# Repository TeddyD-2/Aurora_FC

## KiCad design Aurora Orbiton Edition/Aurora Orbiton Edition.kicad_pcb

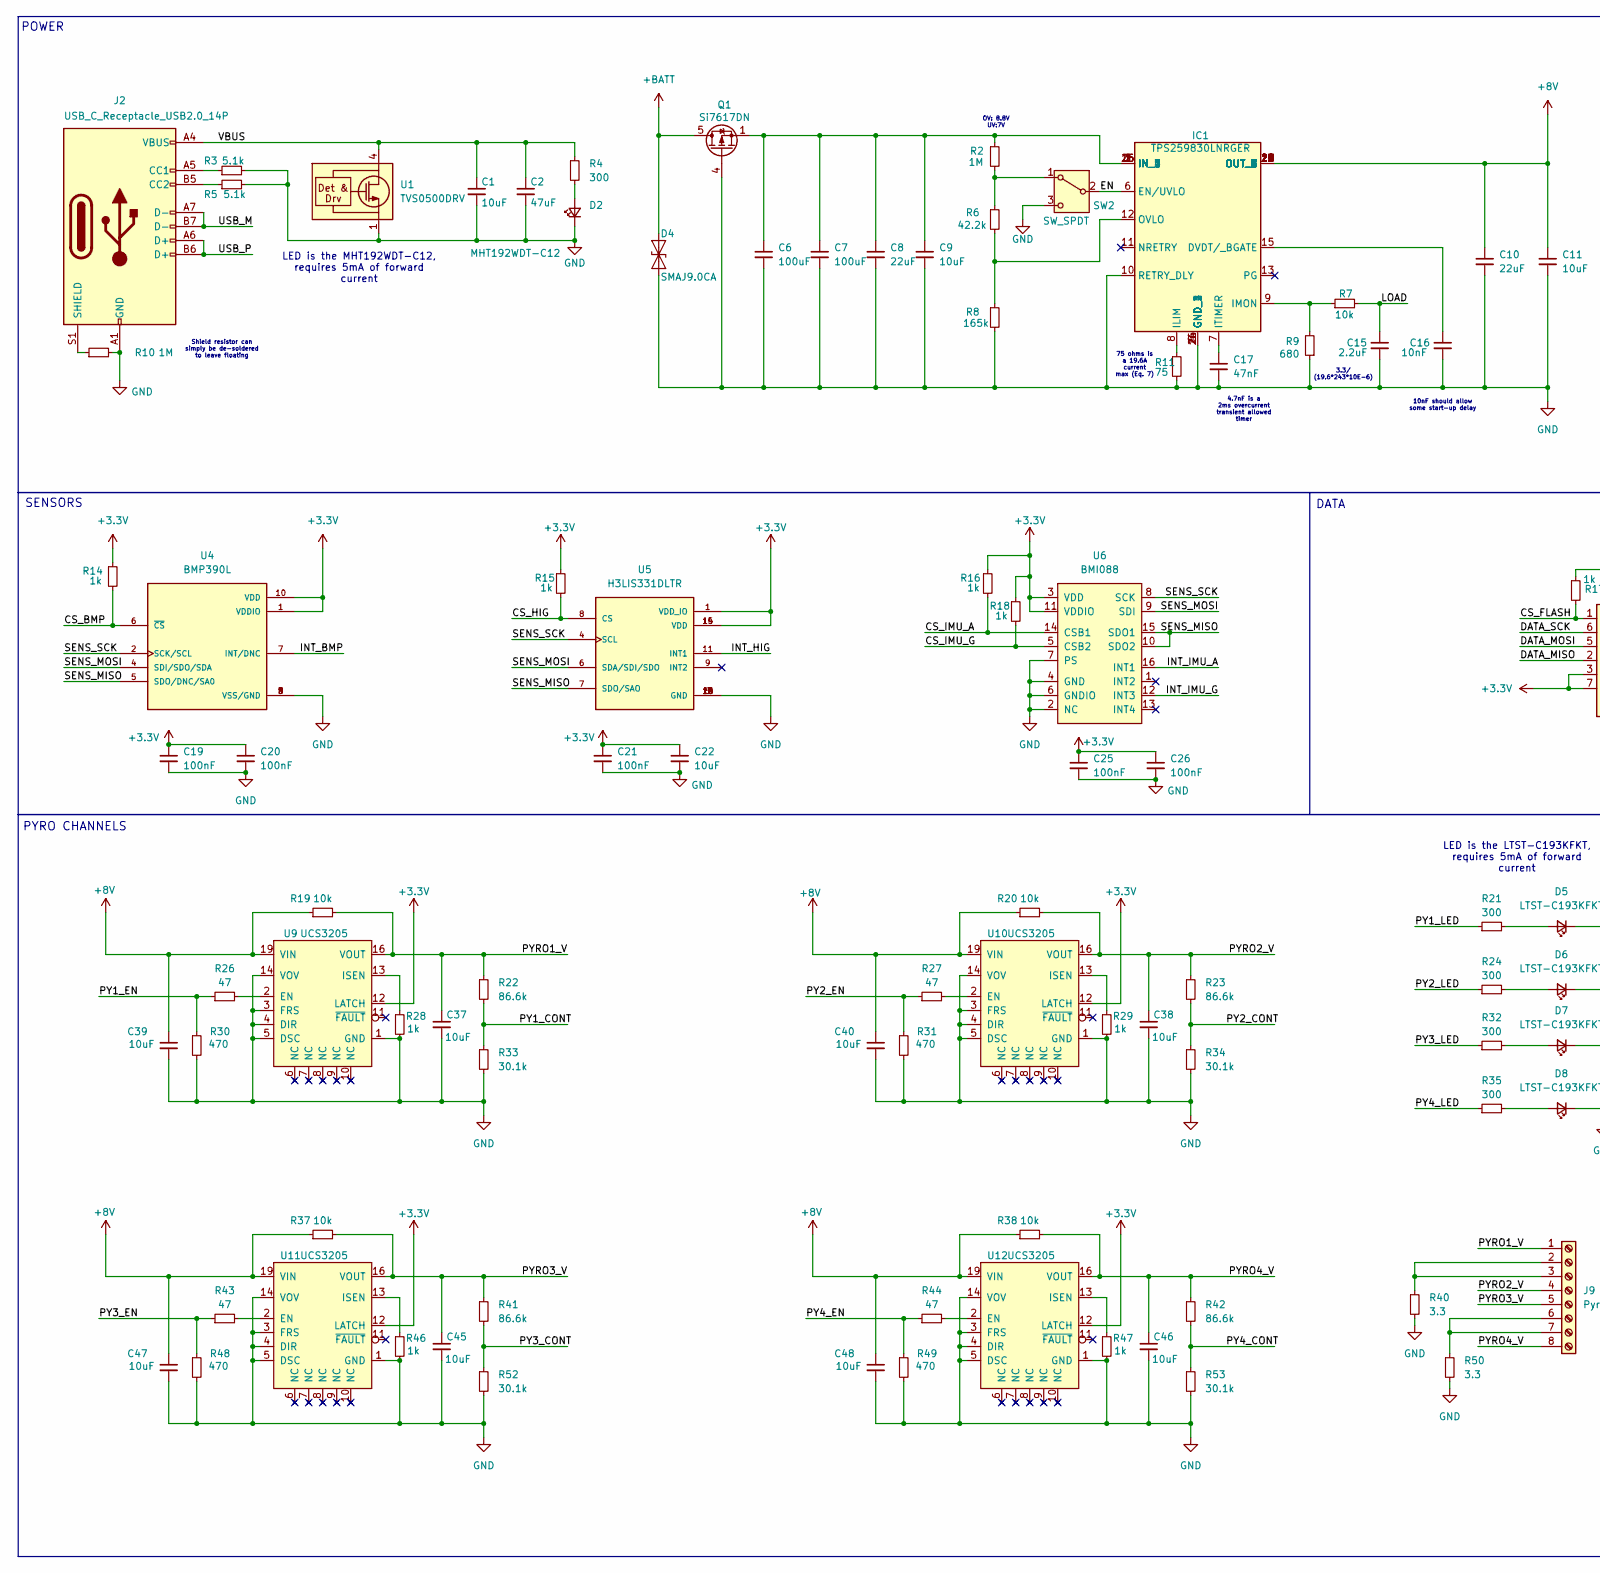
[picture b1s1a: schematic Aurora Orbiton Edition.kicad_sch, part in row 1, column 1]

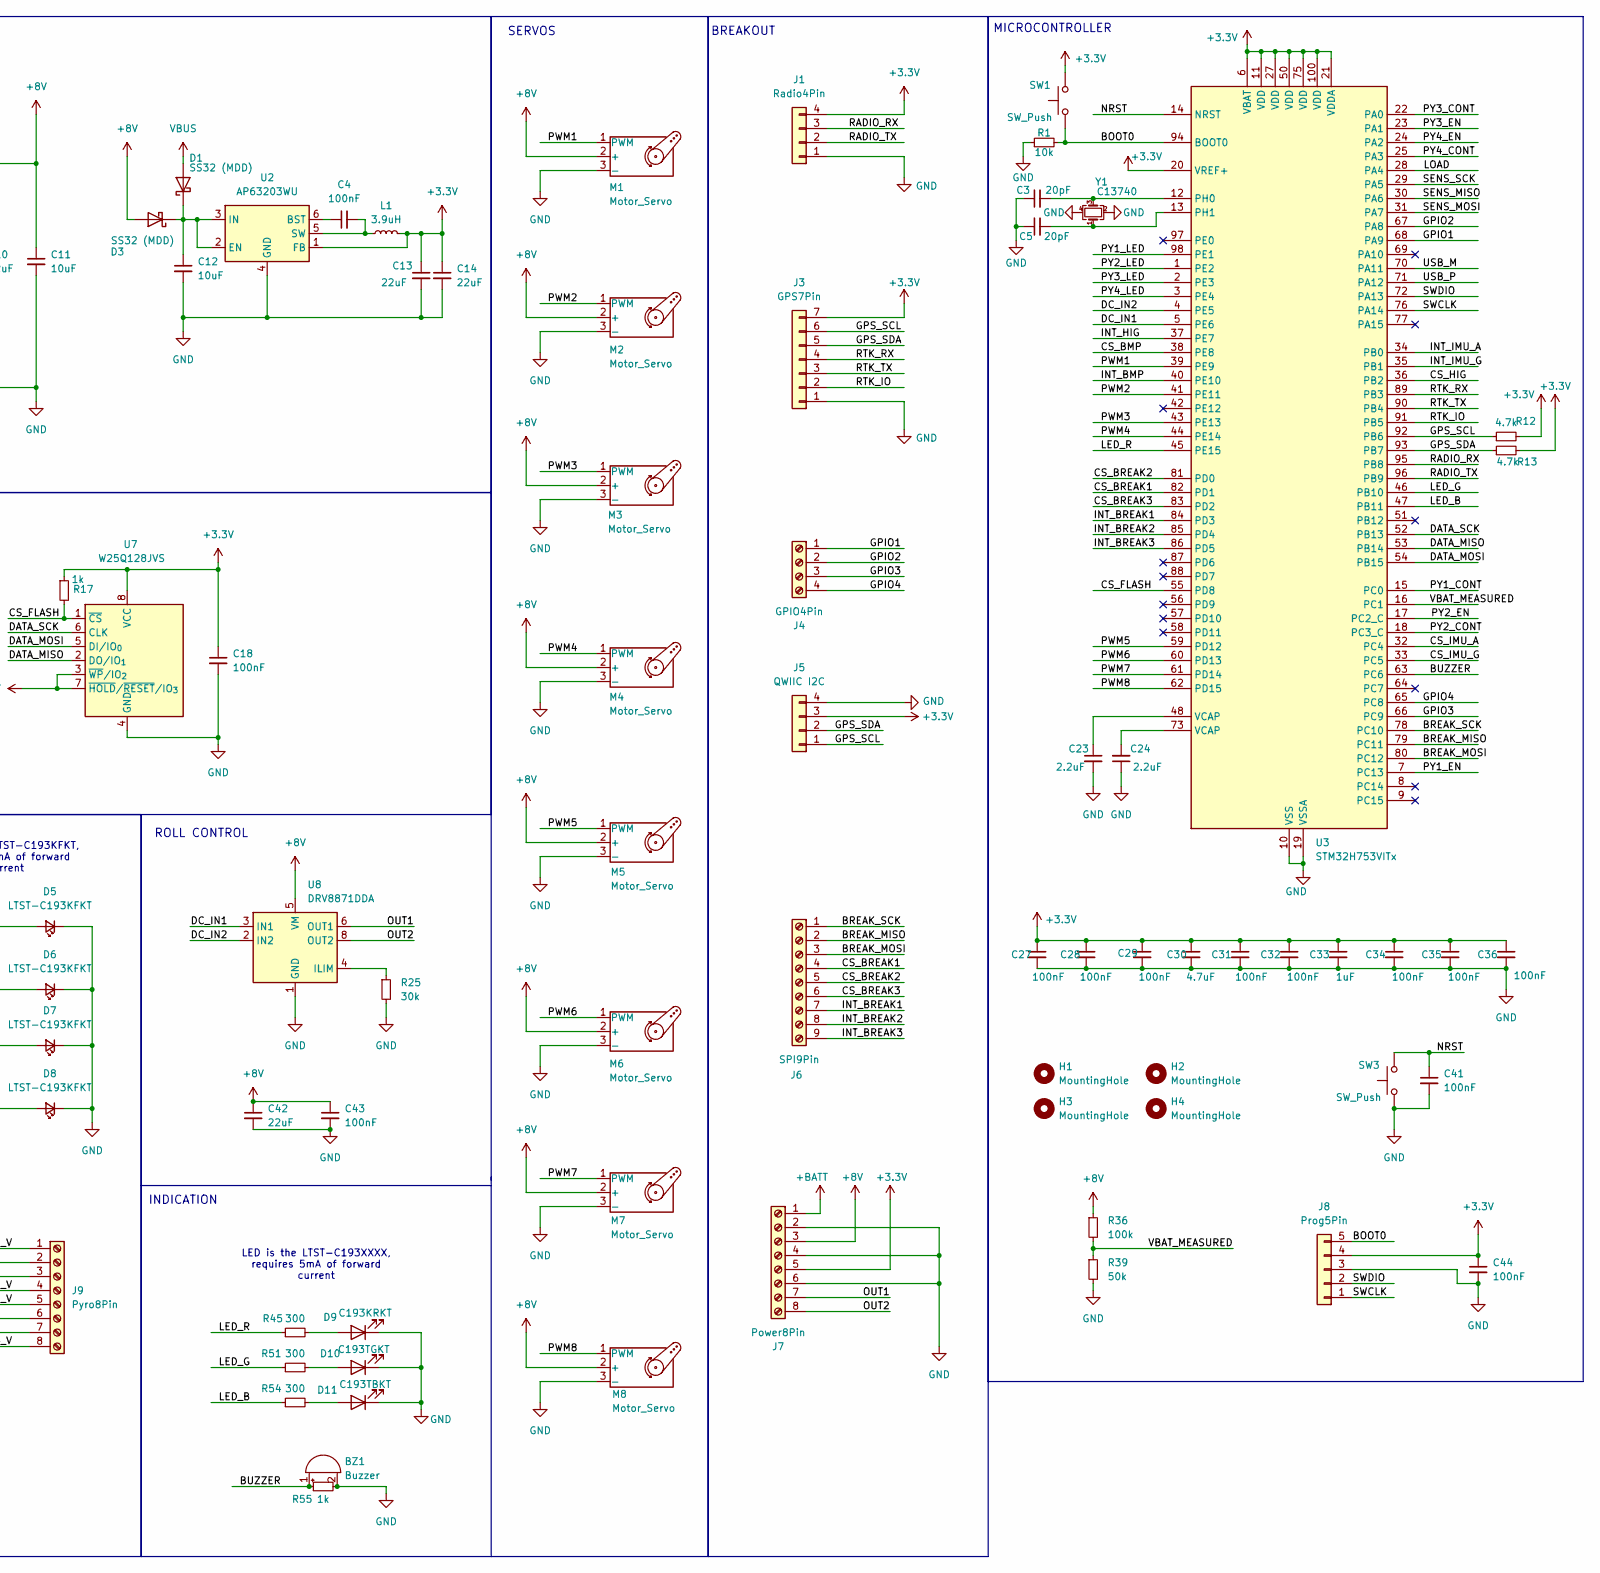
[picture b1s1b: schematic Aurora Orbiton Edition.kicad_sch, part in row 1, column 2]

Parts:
BZ1: Buzzer; Buzzer_CUI_CPT-9019S-SMT
C1, C9, C11, C12, C22, C37, C38, C39, C40, C45, C46, C47, C48: 10uF; C_0603_1608Metric
C2: 47uF; C_0805_2012Metric
C3, C5: 20pF; C_0603_1608Metric
C4, C18, C19, C20, C21, C25, C26, C27, C28, C29, C31, C32, C34, C35, C36, C41, C43, C44: 100nF; C_0603_1608Metric
C6, C7: 100uF; C_1206_3216Metric
C8, C10, C13, C14, C42: 22uF; C_0603_1608Metric
C15, C23, C24: 2.2uF; C_0603_1608Metric
C16: 10nF; C_0603_1608Metric
C17: 47nF; C_0603_1608Metric
C30: 4.7uF; C_0603_1608Metric
C33: 1uF; C_0603_1608Metric
D1, D3: SS32 (MDD); D_SMA
D2: MHT192WDT-C12; D_0603_1608Metric
D4: SMAJ9.0CA; D_SMA
D5, D6, D7, D8: LTST-C193KFKT; D_0603_1608Metric
D9: C193KRKT; D_0603_1608Metric
D10: C193TGKT; D_0603_1608Metric
D11: C193TBKT; D_0603_1608Metric
H1, H2, H3, H4: MountingHole; MountingHole_3mm
IC1: TPS259830LNRGER; Mouser Part Number 595-TPS259830LNRGER
J1: Radio4Pin; JST_SH_BM04B-SRSS-TB_1x04-1MP_P1.00mm_Vertical
J2: USB_C_Receptacle_USB2.0_14P; USB_C_Receptacle_HCTL_HC-TYPE-C-16P-01A
J3: GPS7Pin; JST_SH_BM07B-SRSS-TB_1x07-1MP_P1.00mm_Vertical
J4: GPIO4Pin; TerminalBlock_TE_282834-4_1x04_P2.54mm_Horizontal
J5: QWIIC I2C; JST_SH_BM04B-SRSS-TB_1x04-1MP_P1.00mm_Vertical
J6: SPI9Pin; TerminalBlock_TE_282834-9_1x09_P2.54mm_Horizontal
J7: Power8Pin; TerminalBlock_TE_282834-8_1x08_P2.54mm_Horizontal
J8: Prog5Pin; PinHeader_1x05_P1.27mm_Vertical
J9: Pyro8Pin; TerminalBlock_TE_282834-8_1x08_P2.54mm_Horizontal
L1: 3.9uH; L_Bourns-SRN6028
M1, M2, M3, M4, M5, M6, M7, M8: Motor_Servo; PinSocket_1x03_P2.54mm_Vertical
Q1: Si7617DN; Vishay_PowerPAK_1212-8_Single
R1, R7, R19, R20, R37, R38: 10k; R_0603_1608Metric
R2, R10: 1M; R_0603_1608Metric
R3, R5: 5.1k; R_0603_1608Metric
R4, R21, R24, R32, R35, R45, R51, R54: 300; R_0603_1608Metric
R6: 42.2k; R_0603_1608Metric
R8: 165k; R_0603_1608Metric
R9: 680; R_0603_1608Metric
R11: 75; R_0603_1608Metric
R12, R13: 4.7k; R_0603_1608Metric
R14, R15, R16, R17, R18, R28, R29, R46, R47, R55: 1k; R_0603_1608Metric
R22, R23, R41, R42: 86.6k; R_0603_1608Metric
R25: 30k; R_0603_1608Metric
R26, R27, R43, R44: 47; R_0603_1608Metric
R30, R31, R48, R49: 470; R_0603_1608Metric
R33, R34, R52, R53: 30.1k; R_0603_1608Metric
R36: 100k; R_0603_1608Metric
R39: 50k; R_0603_1608Metric
R40, R50: 3.3; R_2512_6332Metric
SW1, SW3: SW_Push; SW_Push_SPST_NO_Alps_SKRK
SW2: SW_SPDT; SW_SPDT_PCM12
U1: TVS0500DRV; WSON-6-1EP_2x2mm_P0.65mm_EP1x1.6mm
U2: AP63203WU; TSOT-23-6
U3: STM32H753VITx; LQFP-100_14x14mm_P0.5mm
U4: BMP390L; XDCR_BMP390L; PARTREV 1.7
U5: H3LIS331DLTR; QFN300X300X100-16N
U6: BMI088; VQFN16_4.5x3.0mm
U7: W25Q128JVS; SOIC-8_5.3x5.3mm_P1.27mm
U8: DRV8871DDA; Texas_HTSOP-8-1EP_3.9x4.9mm_P1.27mm_EP2.95x4.9mm_Mask2.4x3.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
U9, U10, U11, U12: UCS3205; VQFN19_3.0x3.0mm_2EP
Y1: C13740; OSC-SMD_4P-L3.2-W2.5-BL

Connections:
+3.3V: C13.1, C14.1, C18.1, C19.1, C20.1, C21.1, C22.1, C25.1, C26.1, C27.1, C28.1, C29.1, C30.1, C31.1, C32.1, C33.1, C34.1, C35.1, C36.1, C44.1, J1.4, J3.7, J5.3, J7.5, J8.4, L1.2, R12.2, R13.2, R14.1, R15.1, R16.1, R17.1, R18.1, SW1.2, U2.1 (FB), U3.6 (VBAT), U3.11 (VDD), U3.20 (VREF+), U3.21 (VDDA), U3.27 (VDD), U3.50 (VDD), U3.75 (VDD), U3.100 (VDD), U4.1 (VDDIO), U4.10 (VDD), U5.1 (VDD_IO), U5.14 (VDD), U5.15 (VDD), U6.3 (VDD), U6.11 (VDDIO), U7.3 (~WP/IO_{2}), U7.7 (~HOLD/~RESET/IO_{3}), U7.8 (VCC), U9.12 (LATCH), U10.12 (LATCH), U11.12 (LATCH), U12.12 (LATCH)
+8V: C10.1, C11.1, C39.1, C40.1, C42.1, C43.1, C47.1, C48.1, D3.2 (A), IC1.17 (OUT_1), IC1.18 (OUT_2), IC1.19 (OUT_3), IC1.20 (OUT_4), IC1.21 (OUT_5), IC1.22 (OUT_6), IC1.23 (OUT_7), IC1.24 (OUT_8), J7.3, M1.2 (+), M2.2 (+), M3.2 (+), M4.2 (+), M5.2 (+), M6.2 (+), M7.2 (+), M8.2 (+), R19.1, R20.1, R36.1, R37.1, R38.1, U8.5 (VM), U9.19 (VIN), U9.20 (VOUT), U9.22 (VIN), U10.19 (VIN), U10.20 (VOUT), U10.22 (VIN), U11.19 (VIN), U11.20 (VOUT), U11.22 (VIN), U12.19 (VIN), U12.20 (VOUT), U12.22 (VIN)
+BATT: D4.2 (A2), J7.1, Q1.5 (D)
/BOOT0: J8.5, R1.2, SW1.1, U3.94 (BOOT0)
/BREAK_MISO: J6.2, U3.79 (PC11)
/BREAK_MOSI: J6.3, U3.80 (PC12)
/BREAK_SCK: J6.1, U3.78 (PC10)
/BUZZER: BZ1.1 (+), R55.1, U3.63 (PC6)
/CS_BMP: R14.2, U3.38 (PE8), U4.6 (~CS)
/CS_BREAK1: J6.4, U3.82 (PD1)
/CS_BREAK2: J6.5, U3.81 (PD0)
/CS_BREAK3: J6.6, U3.83 (PD2)
/CS_FLASH: R17.2, U3.55 (PD8), U7.1 (~CS)
/CS_HIG: R15.2, U3.36 (PB2), U5.8 (CS)
/CS_IMU_A: R16.2, U3.32 (PC4), U6.14 (CSB1)
/CS_IMU_G: R18.2, U3.33 (PC5), U6.5 (CSB2)
/DATA_MISO: U3.53 (PB14), U7.2 (DO/IO_{1})
/DATA_MOSI: U3.54 (PB15), U7.5 (DI/IO_{0})
/DATA_SCK: U3.52 (PB13), U7.6 (CLK)
/DC_IN1: U3.5 (PE6), U8.3 (IN1)
/DC_IN2: U3.4 (PE5), U8.2 (IN2)
/EN: IC1.6 (EN/UVLO), SW2.2 (B)
/GPIO1: J4.1, U3.68 (PA9)
/GPIO2: J4.2, U3.67 (PA8)
/GPIO3: J4.3, U3.66 (PC9)
/GPIO4: J4.4, U3.65 (PC8)
/GPS_SCL: J3.6, J5.1, R12.1, U3.92 (PB6)
/GPS_SDA: J3.5, J5.2, R13.1, U3.93 (PB7)
/INT_BMP: U3.40 (PE10), U4.7 (INT/DNC)
/INT_BREAK1: J6.7, U3.84 (PD3)
/INT_BREAK2: J6.8, U3.85 (PD4)
/INT_BREAK3: J6.9, U3.86 (PD5)
/INT_HIG: U3.37 (PE7), U5.11 (INT1)
/INT_IMU_A: U3.34 (PB0), U6.16 (INT1)
/INT_IMU_G: U3.35 (PB1), U6.12 (INT3)
/LED_B: R54.1, U3.47 (PB11)
/LED_G: R51.1, U3.46 (PB10)
/LED_R: R45.1, U3.45 (PE15)
/LOAD: C15.1, R7.2, U3.28 (PA4)
/NRST: C41.1, SW3.2, U3.14 (NRST)
/OUT1: J7.7, U8.6 (OUT1)
/OUT2: J7.8, U8.8 (OUT2)
/PWM1: M1.1 (PWM), U3.39 (PE9)
/PWM2: M2.1 (PWM), U3.41 (PE11)
/PWM3: M3.1 (PWM), U3.43 (PE13)
/PWM4: M4.1 (PWM), U3.44 (PE14)
/PWM5: M5.1 (PWM), U3.59 (PD12)
/PWM6: M6.1 (PWM), U3.60 (PD13)
/PWM7: M7.1 (PWM), U3.61 (PD14)
/PWM8: M8.1 (PWM), U3.62 (PD15)
/PY1_CONT: R22.2, R33.1, U3.15 (PC0)
/PY1_EN: R26.1, R30.1, U3.7 (PC13)
/PY1_LED: R21.1, U3.98 (PE1)
/PY2_CONT: R23.2, R34.1, U3.18 (PC3_C)
/PY2_EN: R27.1, R31.1, U3.17 (PC2_C)
/PY2_LED: R24.1, U3.1 (PE2)
/PY3_CONT: R41.2, R52.1, U3.22 (PA0)
/PY3_EN: R43.1, R48.1, U3.23 (PA1)
/PY3_LED: R32.1, U3.2 (PE3)
/PY4_CONT: R42.2, R53.1, U3.25 (PA3)
/PY4_EN: R44.1, R49.1, U3.24 (PA2)
/PY4_LED: R35.1, U3.3 (PE4)
/PYRO1_V: C37.1, J9.1, R19.2, R22.1, U9.16 (VOUT), U9.17 (VOUT), U9.21 (VOUT)
/PYRO2_V: C38.1, J9.4, R20.2, R23.1, U10.16 (VOUT), U10.17 (VOUT), U10.21 (VOUT)
/PYRO3_V: C45.1, J9.5, R37.2, R41.1, U11.16 (VOUT), U11.17 (VOUT), U11.21 (VOUT)
/PYRO4_V: C46.1, J9.8, R38.2, R42.1, U12.16 (VOUT), U12.17 (VOUT), U12.21 (VOUT)
/RADIO_RX: J1.3, U3.95 (PB8)
/RADIO_TX: J1.2, U3.96 (PB9)
/RTK_IO: J3.2, U3.91 (PB5)
/RTK_RX: J3.4, U3.89 (PB3)
/RTK_TX: J3.3, U3.90 (PB4)
/SENS_MISO: U3.30 (PA6), U4.5 (SDO/DNC/SA0), U5.7 (SDO/SAO), U6.10 (SDO2), U6.15 (SDO1)
/SENS_MOSI: U3.31 (PA7), U4.4 (SDI/SDO/SDA), U5.6 (SDA/SDI/SDO), U6.9 (SDI)
/SENS_SCK: U3.29 (PA5), U4.2 (SCK/SCL), U5.4 (SCL), U6.8 (SCK)
/SWCLK: J8.1, U3.76 (PA14)
/SWDIO: J8.2, U3.72 (PA13)
/USB_M: J2.A7 (D-), J2.B7 (D-), U3.70 (PA11)
/USB_P: J2.A6 (D+), J2.B6 (D+), U3.71 (PA12)
/VBAT_MEASURED: R36.2, R39.1, U3.16 (PC1)
GND: BZ1.2 (-), C1.2, C2.2, C3.1, C5.1, C6.2, C7.2, C8.2, C9.2, C10.2, C11.2, C12.2, C13.2, C14.2, C15.2, C16.2, C17.2, C18.2, C19.2, C20.2, C21.2, C22.2, C23.2, C24.1, C25.2, C26.2, C27.2, C28.2, C29.2, C30.2, C31.2, C32.2, C33.2, C34.2, C35.2, C36.2, C37.2, C38.2, C39.2, C40.2, C41.2, C42.2, C43.2, C44.2, C45.2, C46.2, C47.2, C48.2, D2.1 (K), D4.1 (A1), D5.1 (K), D6.1 (K), D7.1 (K), D8.1 (K), D9.1 (K), D10.1 (K), D11.1 (K), IC1.4 (GND_1), IC1.5 (GND_2), IC1.10 (RETRY_DLY), IC1.14 (GND_3), IC1.26 (GND_4), J1.1, J2.A1 (GND), J2.A12 (GND), J2.B1 (GND), J2.B12 (GND), J3.1, J5.4, J7.2, J7.4, J7.6, J8.3, M1.3 (-), M2.3 (-), M3.3 (-), M4.3 (-), M5.3 (-), M6.3 (-), M7.3 (-), M8.3 (-), Q1.4 (G), R1.1, R3.2, R5.2, R8.2, R9.1, R10.2, R11.2, R25.2, R28.2, R29.2, R30.2, R31.2, R33.2, R34.2, R39.2, R40.2, R46.2, R47.2, R48.2, R49.2, R50.2, R52.2, R53.2, R55.2, SW2.3 (C), SW3.1, U1.1 (GND), U1.2 (GND), U1.3 (GND), U1.7 (GND), U2.4 (GND), U3.10 (VSS), U3.19 (VSSA), U3.26 (VSS), U3.49 (VSS), U3.74 (VSS), U3.99 (VSS), U4.3 (VSS/GND), U4.8 (VSS/GND), U4.9 (VSS/GND), U5.5 (GND), U5.10 (GND), U5.12 (GND), U5.13 (GND), U5.16 (GND), U6.2 (NC), U6.4 (GND), U6.6 (GNDIO), U6.7 (PS), U7.4 (GND), U8.1 (GND), U8.7 (GND), U8.9 (GND), U9.1 (GND), U9.3 (FRS), U9.4 (DIR), U9.5 (DSC), U9.14 (VOV), U9.15 (GND), U10.1 (GND), U10.3 (FRS), U10.4 (DIR), U10.5 (DSC), U10.14 (VOV), U10.15 (GND), U11.1 (GND), U11.3 (FRS), U11.4 (DIR), U11.5 (DSC), U11.14 (VOV), U11.15 (GND), U12.1 (GND), U12.3 (FRS), U12.4 (DIR), U12.5 (DSC), U12.14 (VOV), U12.15 (GND), Y1.2, Y1.4
unnamed: C23.1, U3.48 (VCAP)
unnamed: C24.2, U3.73 (VCAP)
unnamed: C12.1, D1.1 (K), D3.1 (K), U2.2 (EN), U2.3 (IN)
unnamed: D2.2 (A), R4.2
unnamed: D5.2 (A), R21.2
unnamed: D6.2 (A), R24.2
unnamed: D7.2 (A), R32.2
unnamed: D8.2 (A), R35.2
unnamed: D9.2 (A), R45.2
unnamed: D10.2 (A), R51.2
unnamed: D11.2 (A), R54.2
unnamed: C16.1, IC1.15 (DVDT/_BGATE)
unnamed: IC1.8 (ILIM), R11.1
unnamed: IC1.9 (IMON), R7.1, R9.2
unnamed: C6.1, C7.1, C8.1, C9.1, IC1.1 (IN_1), IC1.2 (IN_2), IC1.3 (IN_3), IC1.16 (IN_4), IC1.25 (IN_5), Q1.1 (S), Q1.2 (S), Q1.3 (S), R2.1
unnamed: C17.1, IC1.7 (ITIMER)
unnamed: IC1.12 (OVLO), R6.2, R8.1
unnamed: J2.A5 (CC1), R3.1
unnamed: J2.B5 (CC2), R5.1
unnamed: J2.S1 (SHIELD), R10.1
unnamed: J9.2, J9.3, R40.1
unnamed: J9.6, J9.7, R50.1
unnamed: R2.2, R6.1, SW2.1 (A)
unnamed: C4.1, U2.6 (BST)
unnamed: C4.2, L1.1, U2.5 (SW)
unnamed: C3.2, U3.12 (PH0), Y1.3
unnamed: C5.2, U3.13 (PH1), Y1.1
unnamed: R25.1, U8.4 (ILIM)
unnamed: R26.2, U9.2 (EN)
unnamed: R28.1, U9.13 (ISEN)
unnamed: R27.2, U10.2 (EN)
unnamed: R29.1, U10.13 (ISEN)
unnamed: R43.2, U11.2 (EN)
unnamed: R46.1, U11.13 (ISEN)
unnamed: R44.2, U12.2 (EN)
unnamed: R47.1, U12.13 (ISEN)
VBUS: C1.1, C2.1, D1.2 (A), J2.A4 (VBUS), J2.A9 (VBUS), J2.B4 (VBUS), J2.B9 (VBUS), R4.1, U1.4 (IN), U1.5 (IN), U1.6 (IN)

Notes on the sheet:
LED is the LTST-C193XXXX, requires 5mA of forward current
SENSORS
BREAKOUT
LED is the MHT192WDT-C12, requires 5mA of forward current
4.7nF is a 2ms overcurrent transient allowed timer
MICROCONTROLLER
Shield resistor can simply be de-soldered to leave floating
10nF should allow some start-up delay
OV: 8.8V UV:7V
3.3/ (19.6*243*10E-6)
75 ohms is a 19.6A current max (Eq. 7)
LED is the LTST-C193KFKT, requires 5mA of forward current
DATA
SERVOS
ROLL CONTROL
PYRO CHANNELS
INDICATION
POWER

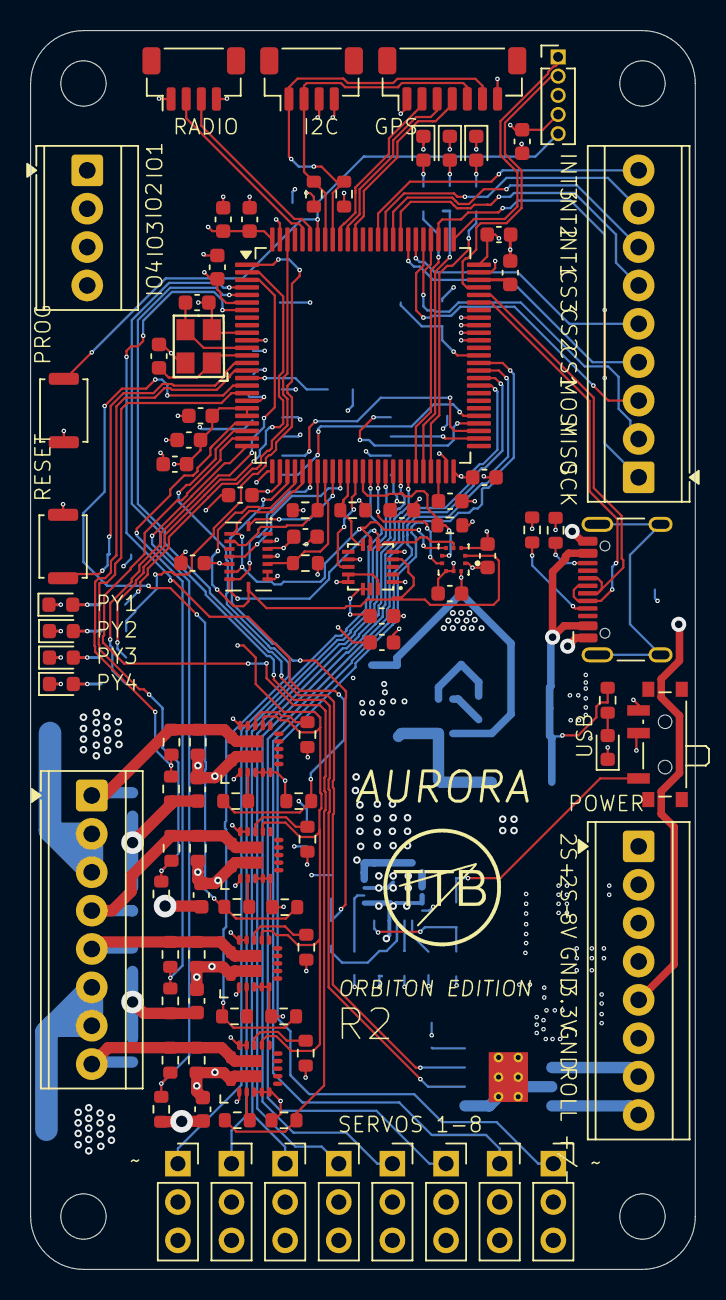
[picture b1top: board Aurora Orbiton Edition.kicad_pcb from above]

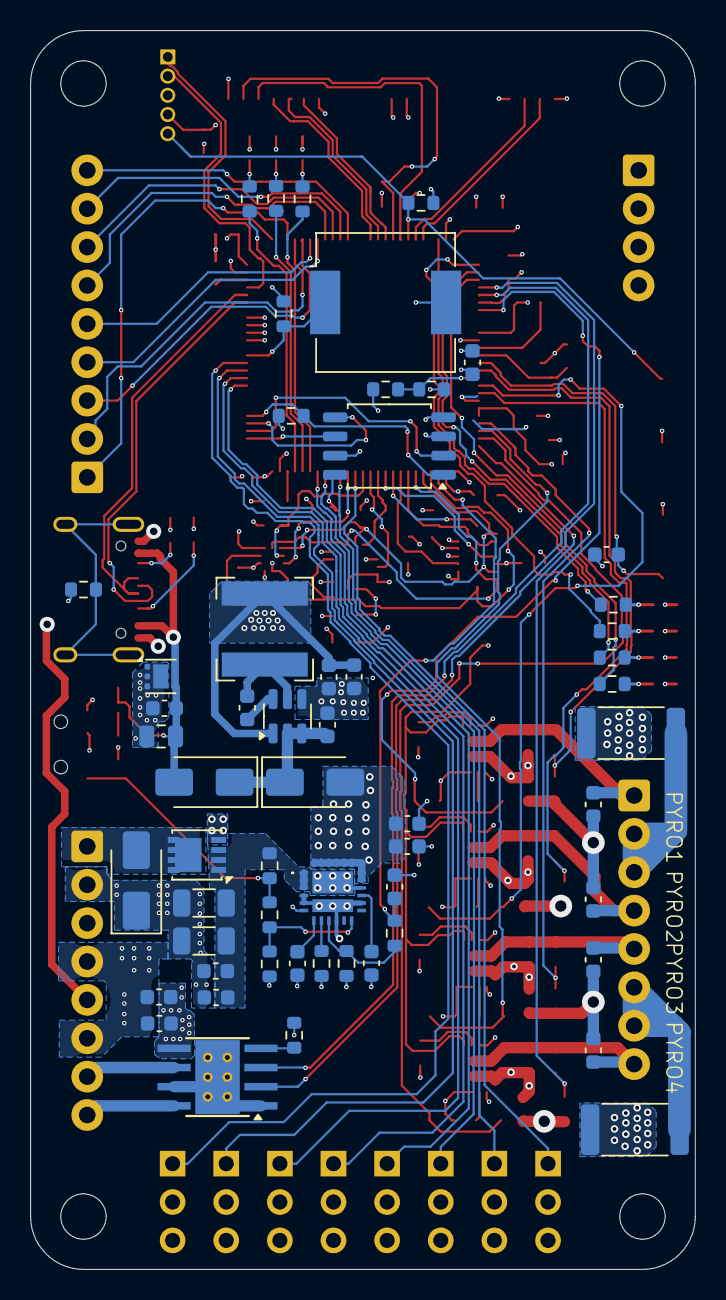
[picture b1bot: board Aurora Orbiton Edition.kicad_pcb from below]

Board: 4 copper layers, 44.0 x 82.0 mm, 155 parts (56 on the bottom side), 117 nets.

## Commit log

2025-09-22 Initial commit of flight computer project
2025-09-22 Test Push
2025-09-22 Updated to R2, unchecked
2025-10-06 Added Image of PCB
2025-10-11 Updated schema pdf
